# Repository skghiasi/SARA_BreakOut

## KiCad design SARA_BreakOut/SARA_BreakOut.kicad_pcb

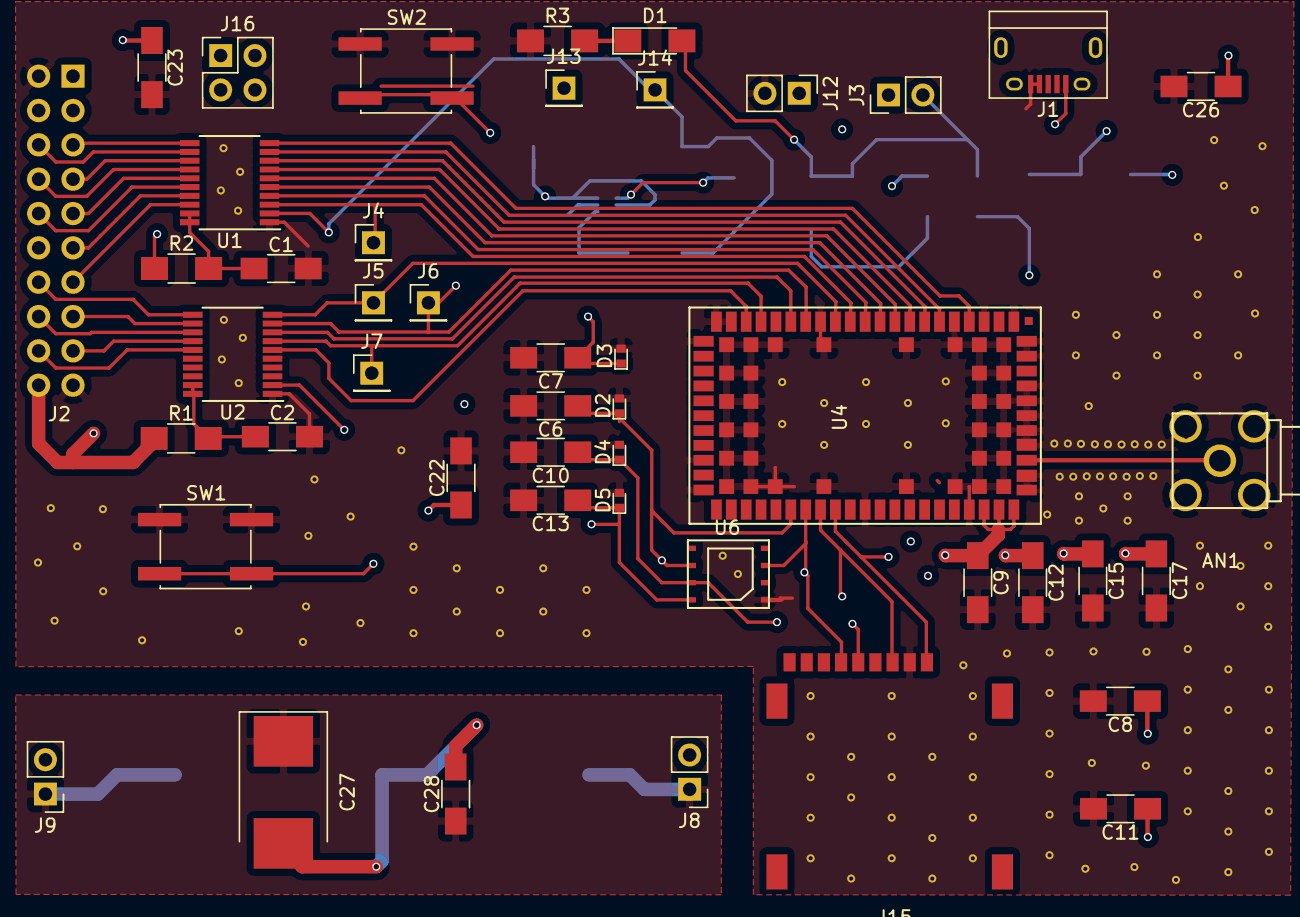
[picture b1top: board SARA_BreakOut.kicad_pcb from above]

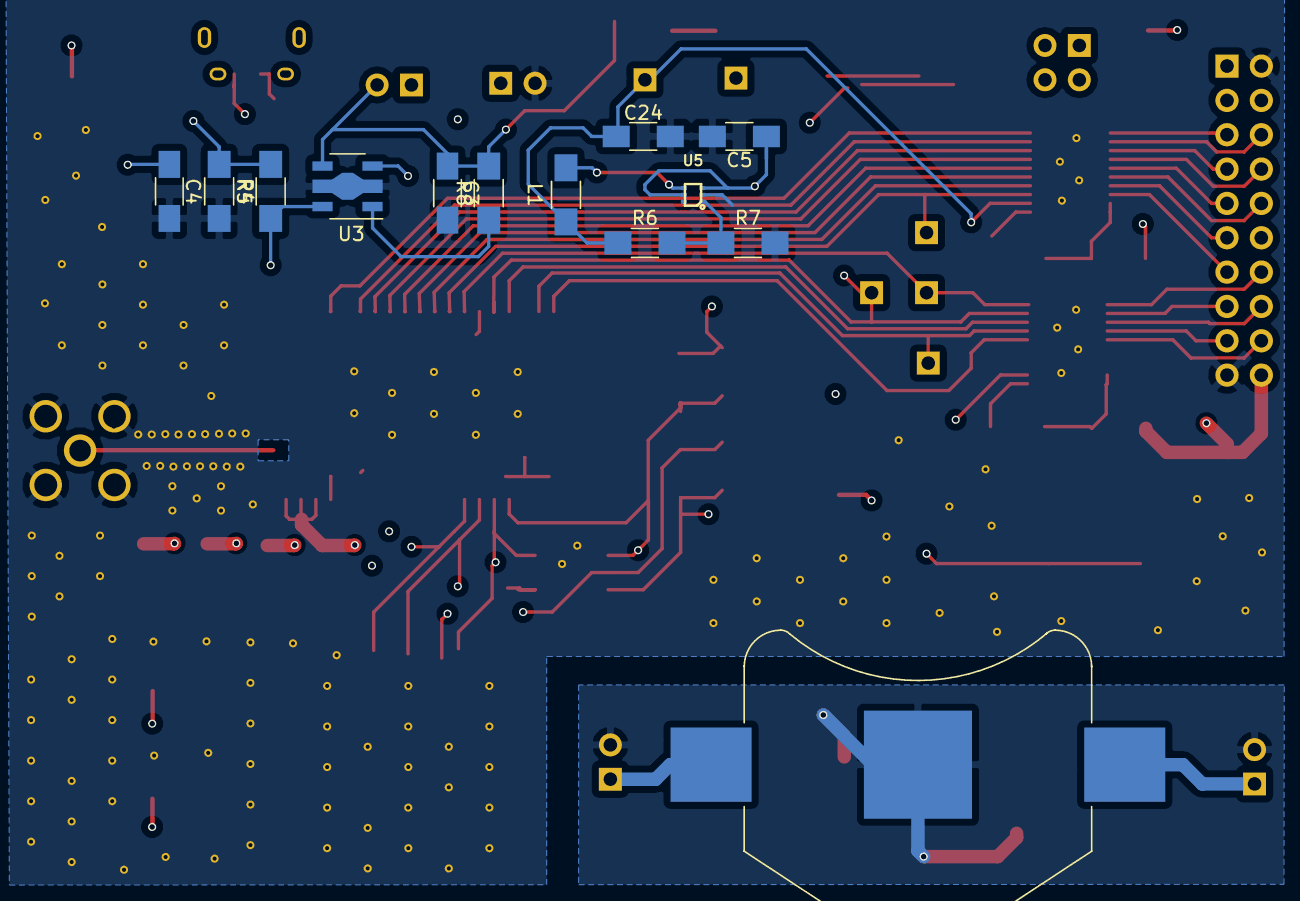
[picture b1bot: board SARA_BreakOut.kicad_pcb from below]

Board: 4 copper layers, 59 parts (13 on the bottom side), 46 nets.

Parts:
AN1: SMA_Amphenon; SMA_TH_Amphenol
BT1: Battery_Cell; Keystone_3008_1x2450-CoinCell
C1, C2: 60pF; C_1206_HandSoldering
C3: 1uF; C_1206_HandSoldering
C4, C24: 22uF; C_1206_HandSoldering
C5: 4.7uF; C_1206_HandSoldering
C6, C7, C10, C13: 47pF; C_1206_HandSoldering
C8, C11, C12: 10nF; C_1206_HandSoldering
C9: 100nF; C_1206_HandSoldering
C15: 68pF; C_1206_HandSoldering
C17: 15pF; C_1206_HandSoldering
C22, C23, C26: 0.1uF; C_1206_HandSoldering
C27: C1_BATT; CP_Tantalum_Case-E_EIA-7260-38_Hand
C28: C2_BATT; C_1206_HandSoldering
D1: LED; LED_1206_HandSoldering
D2, D3, D4, D5: PESD0402; LED_0402
J1: USB_B; USB_Micro-B
J2: Conn_02x10_Odd_Even; right_side_2x10
J3: cur_tp; Pin_Header_Straight_1x02_Pitch2.54mm
J4: txd; Pin_Header_Straight_1x01_Pitch2.54mm
J5: rxd; Pin_Header_Straight_1x01_Pitch2.54mm
J6: pwr_on; Pin_Header_Straight_1x01_Pitch2.54mm
J7: reset_n; Pin_Header_Straight_1x01_Pitch2.54mm
J8: EXT_BATT; Pin_Header_Straight_1x02_Pitch2.54mm
J9: conn_to_board; Pin_Header_Straight_1x02_Pitch2.54mm
J12: Batt_conn; Pin_Header_Straight_1x02_Pitch2.54mm
J13: 3v8 tp; Pin_Header_Straight_1x01_Pitch2.54mm
J14: 1v8 tp; Pin_Header_Straight_1x01_Pitch2.54mm
J15: Mechanical_slot; sim7100_9
J16: 1,2:Vusb_bat/3,4:Vxplain; Pin_Header_Straight_2x02_Pitch2.54mm
L1: 1uH; L_1206_HandSoldering
R1, R6: 200k; R_1206_HandSoldering
R2: 200K; R_1206_HandSoldering
R3: 2k; R_1206_HandSoldering
R4: 41K; R_1206_HandSoldering
R5: 10k; R_1206_HandSoldering
R7: 100k; R_1206_HandSoldering
R8: 47K; R_1206_HandSoldering
SW1, SW2: SW_Push; SW_SPST_EVQQ2
U1, U2: LSF0108; TSSOP-20_4.4x6.5mm_Pitch0.65mm
U3: AP7361C-SOT89-5; SOT-89-5_Housing
U4: SARA-R410M-02B; uBlox_SARA-R4
U5: TLV62568A; SOT563
U6: SWISSCOM_SIM; SWISS_COM_SIMCARD

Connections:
/1v8: C24.1, J14.1, L1.1, R6.1, U1.2, U2.2
/3v8: C4.1, C5.1, C8.1, C9.1, C11.1, C12.1, C15.1, C17.1, C22.1, C23.1, C26.1, J13.1, R4.1, U3.5, U4.51, U4.52, U4.53, U5.3, U5.5
/5v: J1.1, J3.1, J12.1, J16.4
/Batt_and_LEDs/BATT_GND: BT1.2, C27.2, C28.2, J8.2, J9.2
/Batt_and_LEDs/BATT_V: BT1.1, C27.1, C28.1, J8.1, J9.1
/cts: U1.4, U4.11
/dcd: U1.7, U4.8
/dsr: U1.9, U4.6
/dtr: U1.6, U4.9
/gpio1: U2.8, U4.16
/gpio6: U2.6, U4.19
/h_cts: J2.11, U1.17
/h_dcd: J2.8, U1.14
/h_dsr: J2.6, U1.12
/h_dtr: J2.9, U1.15
/h_gpio1: J2.16, U2.13
/h_gpio6: J2.18, U2.15
/h_pwr_on: J2.15, U2.12
/h_reset_n: J2.17, U2.14
/h_ri: J2.7, U1.13
/h_rts: J2.10, U1.16
/h_rxd: J2.14, U2.11
/h_txd: J2.13, U1.18
/h_v_int: J2.5, U1.11
/high_v: J2.20, J16.3, R1.1, R2.1
/main_vin: C3.1, D1.2, J3.2, R8.2, U3.4
/pwr_on: J6.1, SW2.2, U2.9, U4.15
/reset_n: J7.1, SW1.2, U2.7, U4.18
/ri: U1.8, U4.7
/rts: U1.5, U4.10
/rxd: J5.1, U2.10, U4.13
/sim_clk: C6.1, D2.1, J15.3, U4.38, U6.6
/sim_io: C7.1, D3.1, J15.7, U4.39, U6.3
/sim_rst: C10.1, D4.1, J15.2, U4.40, U6.7
/txd: J4.1, U1.3, U4.12
/v_int: U1.10, U4.4
/vsim: C13.1, D5.1, J15.1, U4.41, U6.8
GND: AN1.2, C1.2, C2.2, C3.2, C4.2, C5.2, C6.2, C7.2, C8.2, C9.2, C10.2, C11.2, C12.2, C13.2, C15.2, C17.2, C22.2, C23.2, C24.2, C26.2, D2.2, D3.2, D4.2, D5.2, J1.4, J1.5, J2.2, J2.19, J12.2, J15.5, R3.1, R5.2, R7.2, SW1.1, SW2.1, U1.1, U2.1, U3.2, U4.1, U4.3, U4.5, U4.14, U4.20, U4.21, U4.22, U4.30, U4.32, U4.43, U4.50, U4.54, U4.55, U4.57, U4.58, U4.59, U4.60, U4.61, U4.63, U4.64, U4.65, U4.66, U4.67, U4.68, U4.69, U4.70, U4.71, U4.72, U4.73, U4.74, U4.75, U4.76, U4.77, U4.78, U4.79, U4.80, U4.81, U4.82, U4.83, U4.84, U4.85, U4.86, U4.87, U4.88, U4.89, U4.90, U4.91, U4.92, U4.93, U4.94, U4.95, U4.96, U5.2, U6.1
unnamed: AN1.1, U4.56
unnamed: C1.1, R2.2, U1.19, U1.20
unnamed: C2.1, R1.2, U2.19, U2.20
unnamed: D1.1, R3.2
unnamed: L1.2, U5.4
unnamed: R4.2, R5.1, U3.3
unnamed: R6.2, R7.1, U5.1
unnamed: R8.1, U3.1

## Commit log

2018-06-09 README
2018-06-09 voltage shifter library added, start of the design
2018-06-10 complete SARA breakout for Xplained EXT1
2018-06-12 breakout board, without sim footprint check, no LED and board VCC
2018-06-13 final schem, before starting pcb
2018-06-13 first finish of pcb
2018-06-14 pcb trimmed and shrinked
2018-06-14 final version 1
